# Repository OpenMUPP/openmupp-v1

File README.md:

# OpenMUPP v1 probe board

OpenMUPP v1 is a multi-protocol programming and debug probe.
The design is open hardware.
The board name is `OpenMUPP v1`.
The KiCad 10 project is in this repository.

## What the board does

- It runs **USB CDC, CMSIS-DAP v2 and EDBG (AVR) at the same time** in one firmware image.
- It transfers data **faster than the original Versaloon Mini**. The core runs at 144 MHz, and USB runs at high speed (480 Mbit/s).
- It connects to targets from **1.2 V to 5 V** through level shifters. A 1.2 V target is limited to about 5 MHz.
- It supplies the target with **3.3 V or 5 V (up to about 300 mA)**.
- It makes an adjustable **VPP of 5 V to 14 V** for high-voltage programming of AVR and PIC parts.
- It has **one target connector (J4)**. An adapter board plugs onto J4 and maps it to each target pinout.

## Hardware overview

```mermaid
flowchart LR
    usb["USB-C (J1)"] --> fuse["Polyfuse F1<br/>1.1 A<br/>+5V"]
    fuse --> ldo["3.3 V LDO"]
    fuse --> boost["Boost (U13)<br/>5 V to 14 V"]
    ldo --> mcu["CH32V307RCT6 (U2)<br/>3.3 V"]
    mcu <--> ls["Level shifters<br/>U3 to U6"]
    ls --> esd["33 Ω series resistors<br/>and ESD diodes"]
    esd --> j4["Target connector J4<br/>2 × 10, 2.54 mm"]

    ldo --> tps33["3.3 V target switch<br/>TPS2553 (U12)"]
    fuse --> tps5["5 V target switch<br/>TPS2553 (U14)"]
    tps33 --> vtref(("VTREF"))
    tps5 --> vtref
    vtref --> j4

    boost --> vpp["VPP switch<br/>P-FET (Q2)"]
    vpp --> j4
    pd["Pin 19 pull-down<br/>N-FET (Q6), pull-up to VTREF"] --> j4

    mcu -- "TARGET_PWR_EN" --> tps33
    mcu -- "TARGET_5V_EN" --> tps5
    mcu -- "VPP_12V_ADJ<br/>(DAC: 5 V to 14 V)" --> boost
    mcu -- "VPP_EN, VPP_ON" --> vpp
    mcu -- "VPP_PD" --> pd
    boost -- "VPP_SENSE" --> mcu
```

| Block | Part | Notes |
|-------|------|-------|
| MCU | CH32V307RCT6, LQFP64 (U2) | QingKe V4F RISC-V, 144 MHz, 256 KB flash, 64 KB SRAM. 8 MHz crystal (Y1). |
| USB | USB-C receptacle (J1), USBLC6-2SC6 (U1) | USB 2.0 high speed (USBHS on PB6, PB7). 5.1 kΩ CC resistors. |
| 3.3 V rail | XC6220B331MR-G LDO | Supplies the MCU and the target power switch. |
| VBUS protection | 1.1 A polyfuse (F1), 2.2 A trip, 16 V | At 4.75 V VBUS, expect `+5V` at about 4.6 V or more at full load. See [Target power](docs/hardware.md#target-power). |
| Target power (3.3 V or 5 V) | TPS2553 (U12, 3.3 V), TPS2553 (U14, 5 V), FDV301N interlock (Q4) | Current limit about 300 mA (ILIM 91 kΩ) on each rail. Both outputs join `VTREF`. See [Target power](docs/hardware.md#target-power). |
| VPP (5 V to 14 V) | MT3608 boost (U13), AO3401A P-FET (Q2), FDV301N driver (Q3), MMBT3906 current limit (Q5), FDV301N pull-down (Q6) | The firmware sets the level with the DAC on PA5 (`VPP_12V_ADJ`). Current limit about 17 mA. Pin 19 has three states: 0 V, `VTREF` and VPP. See [High voltage (VPP)](docs/hardware.md#high-voltage-vpp). |
| Level shifters | SN74LXC8T245 (U3, U4), SN74LXC1T45 (U5, U6) | All parts work from 1.1 V to 5.5 V. |
| Reset path | FDV301N (Q1), U4 channel 4 | Q1 pulls nRESET low. U4 reads the line back. |
| ESD | TPD4E05U06 (U8 to U10) | On all J4 signals except the supplies. |
| Probe debug | J3 (5-pin SWD), J2 (3-pin UART) | J3 debugs the probe MCU only. J2 is the log port of the probe firmware. **They are not target connectors.** |
| User I/O | SW1 (key and BOOT0), LEDs D1 (blue) and D4 (red) for state, D2 (green) for USB | |

### Target connector J4

J4 is a 2 × 10 IDC header, 2.54 mm. The footprint in the schematic is `Connector_IDC:IDC-Header_2x10_P2.54mm_Horizontal`. Use a shrouded and keyed header. VPP is on pin 19, so a shifted plug must not fit.

| Pin | Signal | Pin | Signal |
|-----|--------|-----|--------|
| 1 | `VTREF`: target voltage sense, and target supply when the probe powers the target | 2 | Reserved (no connect) |
| 3 | GND | 4 | TMS / SWDIO / data (`DIR_SWDIO`) |
| 5 | GND | 6 | TCK / SWCLK / SCK |
| 7 | GND | 8 | TDO / SWO / MISO |
| 9 | GND | 10 | TDI / MOSI |
| 11 | RTCK | 12 | nRESET / debugWIRE, open-drain |
| 13 | UART TX (probe output) | 14 | UART RX (probe input) |
| 15 | TRST | 16 | Adapter ID (ADC, 3.3 V domain) |
| 17 | `AUX1` | 18 | `AUX2` |
| 19 | VPP (0 V, `VTREF`, or 5 V to 14 V) | 20 | GND |

- **Target power is on pin 1.** One pin carries the sense and the supply. The limit is about 300 mA at 3.3 V and at 5 V.
- **Pin 2 is reserved.** A later adapter that needs a second supply pin can use it, with its own switch.
- **Pin 16 goes to the adapter only.** It never goes to the target.

### Adapter boards and adapter ID

An adapter board has connectors, wires and one ID resistor. The resistor goes from J4 pin 16 to GND. R30 (10 kΩ) pulls pin 16 up to 3.3 V. The firmware reads the ratio x = R<sub>ID</sub> / (R<sub>ID</sub> + 10 kΩ) on PB1. The ADC reference and R30 share the 3.3 V rail, so supply drift cancels. R44 (10 kΩ) in series and D5 (BAT54 Schottky diode) to 3.3 V protect PB1 (net `ADAPTER_ID_MCU`). They work when a 5 V target supply is on pin 16 by mistake. C13 (100 nF) from `ADAPTER_ID_MCU` to GND filters the ADC input. The firmware must use a long ADC sample time and keep the internal pull resistors off.

The AVR 10-pin connector uses the Atmel-ICE pinout. Three passive variants route the data pin to SWDIO:

| Variant | Protocols | Slot |
|---------|-----------|------|
| A | JTAG, ISP, debugWIRE | 1 |
| B | PDI | 2 |
| C | TPI, UPDI, aWire | 3 |

| Slot | R<sub>ID</sub> (E24, 1 %) | x | Accept window | Use |
|------|------------------|-------|---------------|-----|
| — | 0 Ω (short) | 0.000 | below 0.05 | Fault: pin 16 shorted to GND |
| 1 | 1.1 kΩ | 0.099 | 0.05 to 0.15 | Variant A |
| 2 | 2.4 kΩ | 0.194 | 0.15 to 0.25 | Variant B |
| 3 | 4.3 kΩ | 0.301 | 0.25 to 0.35 | Variant C |
| 4 | 6.8 kΩ | 0.405 | 0.35 to 0.45 | Arm adapter |
| 5 | 10 kΩ | 0.500 | 0.45 to 0.55 | Pin-header adapter |
| 6 | 15 kΩ | 0.600 | 0.55 to 0.65 | Free |
| 7 | 24 kΩ | 0.706 | 0.65 to 0.75 | Free |
| 8 | 39 kΩ | 0.796 | 0.75 to 0.85 | AVR high-voltage adapter |
| 9 | 91 kΩ | 0.901 | 0.85 to 0.95 | PIC high-voltage adapter |
| — | open | 1.000 | above 0.95 | No adapter |

The worst-case error is about 0.007 in x, and the windows are ±0.05 wide. The firmware treats a free slot as "unknown adapter". The firmware enables VPP only for slots 8 and 9.

The adapter schematics are in [connectors/](connectors/README.md). Each adapter has a female 2 × 10 header that plugs directly onto J4. No ribbon cable is necessary.

See [docs/hardware.md](docs/hardware.md) for the sheets, level shifting, target power, VPP and the MCU pin map.

## Firmware

The firmware is the `openmupp` project. The CH32V307 has a ROM bootloader. It can program the flash through USART1 or USB (WCH ISP protocol). Hold SW1 (BOOT0) during reset to start it. The firmware port to the CH32V307 is in progress. A firmware jump to the bootloader is not available yet.

Related repositories:

- Firmware: <https://github.com/OpenMUPP/openmupp>
- Drivers: <https://github.com/armint/ch32v00x-system> and <https://github.com/armint/ch32v00x-art>

## Getting started

### Requirements

- KiCad 10.0.6 or newer.
- The shared footprint libraries. They are not public. The PCB file has a copy of each footprint, so you can open and edit the board without them. The project uses the nicknames `resistors`, `capacitors`, `headers`, `connectors`, `inductors` and `sot`. The stock KiCad libraries (`Package_*`, `Connector_IDC`, `Diode_SMD`, `LED_SMD`, `Crystal`, `Fuse`, `Button_Switch_SMD`) must also be present.

### Open the project

1. Clone this repository.
2. Open `openmupp-v1.kicad_pro`.

The board and the schematic open without the shared footprint libraries. To change a footprint, edit the copy in the PCB file.

The project symbol library `openmupp-v1` is in the repository. `sym-lib-table` links it with `${KIPRJMOD}`.

### Conventions

- **Reference designators are unique across all sheets.** Check before you add a part.
- **Every part has an `LCSC` field** for JLCPCB assembly. Prefer parts from the JLCPCB basic library. Each extended part costs a setup fee.
- **Small N-FETs:** use the FDV301N (LCSC C15310). V<sub>GS(th)</sub> is 1.06 V maximum, so a gate drive of 1.8 V turns it on. The limits are 25 V V<sub>DS</sub> and 8 V V<sub>GS</sub>.
- **Footprints:** check the pads against the datasheet land pattern.
- **Checks:** run ERC after each change. Look for shorted nets and for unconnected pins.

## License

Copyright Armin van der Togt 2026.

This design is licensed under the CERN Open Hardware Licence Version 2 - Strongly Reciprocal (CERN-OHL-S-2.0). See [LICENSE](LICENSE).
The design has no warranty. Refer to the licence for the applicable conditions.

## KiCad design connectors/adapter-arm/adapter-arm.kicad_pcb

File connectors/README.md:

# Target adapters for OpenMUPP v1

Each folder is a KiCad 10 project with the schematic of one target adapter. The projects have no board layout yet.

| Folder                                     | Adapter          | Slot | R<sub>ID</sub> | Target connectors                                              |
|--------------------------------------------|------------------|------|----------------|----------------------------------------------------------------|
| [adapter-avr-jtag-isp](adapter-avr-jtag-isp/) | AVR variant A | 1 | 1.1 kΩ | Atmel-ICE 10 (1.27 mm), AVR JTAG 10 (2.54 mm), 2 × 3 ISP |
| [adapter-arm](adapter-arm/)                | Arm              | 4    | 6.8 kΩ         | ARM JTAG 20, Cortex Debug 10, STDC14                           |
| [adapter-pin-header](adapter-pin-header/)  | Pin header       | 5    | 10 kΩ          | 1 × 6 SWD / CH32 / SWIM, 1 × 4 ST SWIM, 2 × 5 WCH-LinkE layout |
| [adapter-avr-hv](adapter-avr-hv/)          | AVR high voltage | 8    | 39 kΩ          | DIP-8 and DIP-14 sockets (HVSP), 2 × 3 TPI and UPDI            |
| [adapter-pic-hv](adapter-pic-hv/)          | PIC high voltage | 9    | 91 kΩ          | PICkit ICSP 1 × 6                                              |

The slot table and the J4 pinout are in the [main README](../README.md#adapter-boards-and-adapter-id).

## Rules for all adapters

1. J1 is a female 2 × 10 header, 2.54 mm. It plugs directly onto J4 of the probe. The pin numbers of J1 are the J4 pin numbers.
2. One 1 % resistor (R1) goes from J1 pin 16 to GND. J1 pin 16 never goes to the target.
3. J1 pin 2 (reserved) stays open. J1 pin 19 (VPP) stays open on each adapter that is not a high-voltage adapter.
4. Each adapter has a 1 × 4 debug UART header: 1 GND, 2 RX (probe input), 3 TX (probe output), 4 `VTREF`. The labels are from the probe side. Pins 1 to 3 have the same order as J2 on the main board. Pin 4 lets the UART work without a debug connector to the target.
5. Connect only one target connector at a time.

## Female header on J4

J4 on the probe is a shrouded, right-angle header (`IDC-Header_2x10_P2.54mm_Horizontal`). The adapter schematics use `PinSocket_2x10_P2.54mm_Horizontal` for J1, so the adapter board is in the same plane as the probe. Before layout, check these items:

- **Fit.** The socket body must go into the shroud of J4. Measure the shroud opening and the socket body.
- **Pin mirror.** The socket and the header mate face to face. Make sure that J1 pin 1 touches J4 pin 1 in the layout.
- **Polarity.** A plain socket has no key, so it can go in rotated by 180°. Then J1 pin 16 touches a probe GND pin, and the probe pin 16 touches an adapter GND pin. The adapter ID reads 0 Ω (the fault slot). The firmware must then keep the shifter outputs, the target power and VPP off. Use a keyed socket, or add a mechanical key on the adapter board, if possible.

## RESET and MCLR on J4 pin 19

`adapter-avr-hv` and `adapter-pic-hv` connect the target RESET or MCLR pin directly to J1 pin 19. The nets are `RESET_VPP` and `MCLR_VPP`. The probe gives pin 19 three levels: 0 V (reset), `VTREF` (run) and VPP (program). See [Pin 19 states](../docs/hardware.md#pin-19-states). Thus the adapters have no reset circuit, and J1 pin 18 (`AUX2`) is not used.

HVSP entry needs RESET at 0 V while `VCC` comes up. Then RESET must go to 12 V after a short time. Q6 on the probe holds pin 19 at 0 V. The firmware can set `VPP_ON` before `VCC` comes up, because Q6 holds pin 19 low against the current limit. Then the firmware releases Q6 at the time that the data sheet gives. Pin 19 then goes to VPP in some µs.

## UPDI on J4 pin 12

UPDI uses J4 pin 12 (nRESET / debugWIRE), not J4 pin 4 (SWDIO). The reasons:

- The UPDI pin of a tinyAVR is a weak driver. The ATtiny1614/16/17 data sheet (DS40002204A, table 36-16, VOL2) guarantees only 0.1 mA at 1.8 V and 0.5 mA at 5 V.
- J4 pin 4 has a 2.2 kΩ pull-up on the probe. The target must then sink 0.8 mA to 2.3 mA. See issue [#6](https://github.com/OpenMUPP/openmupp-v1/issues/6).
- J4 pin 12 has a 10 kΩ pull-up. The target must sink 0.18 mA at 1.8 V and 0.5 mA at 5 V.
- J4 pin 12 is open-drain (Q1 on the probe). This is the physical layer that UPDI expects.

Effects on the firmware:

- The read-back of J4 pin 12 goes to PB11 (USART3_RX). The USART receives UPDI and sees its own transmit.
- The CH32V307 USART cannot invert TX, so the firmware sends UPDI in software through Q1 (PB12). debugWIRE uses the same method.
- The rise time with 10 kΩ and about 30 pF to 50 pF is about 0.3 µs to 0.5 µs. This is sufficient for 225 kbps (the maximum UPDI rate at 1.8 V). It is not sufficient for 0.9 Mbps. These values are estimates, not measurements.
- The debug UART (J4 pins 13 and 14) stays free during UPDI.

On `adapter-avr-hv`, TPI data also uses J4 pin 12, through the same path as UPDI. The TPIDATA pin of the ATtiny4/5/9/10 has an internal pull-up in TPI mode (20 kΩ to 50 kΩ). The target drives a 0 and the first 1 of a sequence. Then the pull-up holds the line high (ATtiny4/5/9/10 data sheet DS40002060A, section 15.3.8). Thus TPI and UPDI see the same physical layer: open drain with a pull-up. Other TPI adapters can still use J4 pin 4.

## UPDI high-voltage pulse

`adapter-avr-hv` has one 2 × 3 header (J4) for TPI and UPDI. JP1, a 2-pin jumper header, selects the pin that gets the high voltage (HV):

| JP1 | Use | Pin 1 (data) | Pin 5 | HV goes to |
|-----|-----|--------------|-------|------------|
| Open | TPI (ATtiny4/5/9/10). UPDI with a separate RESET pin, for example AVR DD. | `UPDI_HV` (through Q2 to J1 pin 12) | `RESET_VPP` (J1 pin 19) | Pin 5 |
| Closed | UPDI with HV on the UPDI pin (tinyAVR 0, 1 and 2 series) | `UPDI_HV` (through Q2 to J1 pin 12) | `RESET_VPP` (J1 pin 19) | Pin 1 and pin 5 |

On the tinyAVR 0, 1 and 2 series, the UPDI pin and the RESET pin are the same pin. The data sheet calls the HV entry "UPDI Enable with High-Voltage Override of RESET Pin". The HV detection level (V<sub>HVRST</sub>) is 11.5 V to 12.5 V. The AVR DD setting is not verified against a part. Check the data sheet of each part before you use it.

The TPIDATA pin and the AVR DD UPDI pin must not get 12 V. Thus JP1 must be open for these parts. With JP1 closed, pin 5 also gets VPP. On a tinyAVR target board, pin 5 is usually not connected, so this is permitted. Some target boards connect pin 5 to the UPDI pin. Then pin 19 at 0 V holds the UPDI line low. Check the target board before you use it.

The parts of the UPDI path:

1. D2 (BAT54W) and JP1 connect J1 pin 19 to `UPDI_HV` when JP1 is closed. D2 has a drop of about 0.3 V. Set VPP to about 12.3 V for 12 V on the UPDI pin. `RESET_VPP` has no diode, so it gets VPP directly.
2. Q2 (FDV301N) is a pass switch between `UPDI_HV` (drain) and `UPDI` (source, J1 pin 12). The gate is on `VTREF`. When `UPDI_HV` is at 12 V, Q2 is off and the 10 kΩ pull-up on the probe holds `UPDI` at `VTREF`. The body diode is then reverse biased. The ESD diode on J4 pin 12 of the probe clamps at about 6 V, so this protection is necessary.
3. While VPP is off, Q2 passes UPDI and TPI data in both directions. The probe pulls `UPDI` high (10 kΩ). The internal pull-up of the target pulls `UPDI_HV` high. The adapter has no pull-up on `UPDI_HV`, so it adds no load to the weak UPDI pad.
4. With JP1 closed, keep pin 19 at 0 V (`VPP_PD` high) during UPDI, except during the HV pulse. In the run state, pin 19 is at `VTREF`. Then R39 on the probe and D2 pull `UPDI_HV` up. When the target sends a 0, it must also sink this current: about 0.13 mA at 1.8 V and 0.45 mA at 5 V. The UPDI pad guarantees only 0.1 mA at 1.8 V. At 0 V on pin 19, D2 blocks and adds no load.
5. The firmware can read the JP1 position before it sets VPP on. Put pin 19 in the run state and set Q1 on. With JP1 closed, current flows from R39 through D2, Q2 and Q1. `VPP_SENSE2` then reads less than about 0.5 V. With JP1 open, `VPP_SENSE2` reads the run level. If the JP1 position does not agree with the selected target, the firmware must not set VPP on. This value is an estimate, not a measurement.

Limits:

- Q2 passes a low level only when `VTREF` is above V<sub>GS(th)</sub>. The FDV301N has 1.06 V maximum, so `VTREF` of 1.8 V is sufficient. The tinyAVR parts run from 1.8 V to 5.5 V.
- The gate-source voltage of the FDV301N must stay above −0.3 V. The source (`UPDI`) has a 10 kΩ pull-up to the gate potential (`VTREF`), so it does not go above the gate. Q2 leakage (I<sub>DSS</sub> 1 µA maximum at 20 V) moves `UPDI` by about 10 mV.
- A low-to-high edge on `UPDI_HV` above `VTREF` − V<sub>GS(th)</sub> comes from the target pull-up only. This is slower than on `UPDI`. Check the rise time at the UPDI baud rate and at the TPI clock rate.
- VPP goes to `RESET_VPP`. With JP1 closed, it also goes to `UPDI_HV` at the same time. Connect only one target to J2, J3 or J4.
- After the pulse, the line must return to the normal level quickly: the debugger drives it low 1 µs to 10 µs after the HV ends (data sheet figure 33-6). D2 cannot pull `UPDI_HV` down. The probe pulls J4 pin 12 low through its Q1. The adapter Q2 then conducts, because its gate is at `VTREF`, and pulls `UPDI_HV` low. At the same time, Q6 on the probe pulls pin 19 to 0 V in less than 1 µs, so D2 blocks at once.
- The TPS2553 on the probe has a soft start of some milliseconds. Check the pulse timing in the target data sheet.

## HVSP pull-downs

HVSP entry needs the three Prog_enable pins at 0 while `VCC` comes up. R4 to R7 (10 kΩ) hold them low on `adapter-avr-hv`. These resistors are not in the adapter plan. The pins come from the ATtiny datasheets:

| Part              | Prog_enable[0..2]           | Resistors                                          |
|-------------------|-----------------------------|----------------------------------------------------|
| ATtiny13/25/45/85 | SDI, SII, SDO (PB0 to PB2)  | The probe drives SDI and SII low. R4 holds SDO low |
| ATtiny24A/44A/84A | PA0, PA1, PA2 (pins 13, 12, 11) | R5, R6, R7                                     |

J4 pin 8 (SDO input) is an input only, so the probe cannot hold SDO low. The target drives SDO against R4 after entry.

## Items to check before layout

- **WCH-LinkE layout.** The positions of GND, 3V3 and 5V on the WCH-LinkE header come from the schematic text only. Check them on a real WCH-LinkE. Pin 8 (3V3) connects to `VTREF`. Pin 10 (5V) stays open.
- **ST SWIM order.** Check the order (VDD, SWIM, GND, NRST) against ST UM1075.
- **1.27 mm headers.** Cortex Debug 10 and STDC14 use plain 1.27 mm pin headers in the schematic. Use shrouded, keyed parts (Samtec FTSH-105 and FTSH-107, or equal). Put their footprints in the `kicad-footprints` repository.
- **Atmel-ICE 10.** J2 on `adapter-avr-jtag-isp` is a plain 1.27 mm pin header in the schematic. Use a shrouded, keyed part, as for Cortex Debug 10. J4 (AVR JTAG 10, 2.54 mm) uses a shrouded IDC header.
- **Footprint libraries.** All resistors are 0603 and use `resistors:R_0603` from the `kicad-footprints` repository, as on the main board.

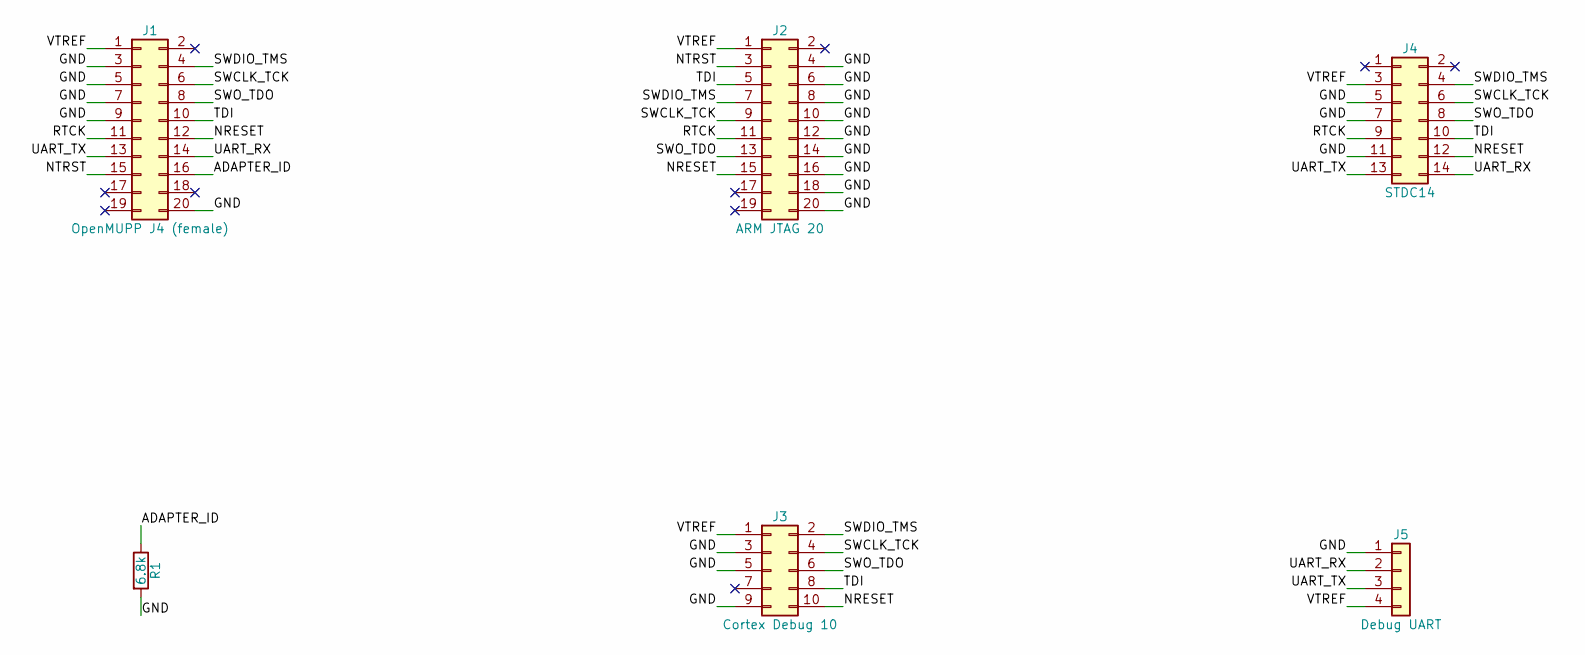
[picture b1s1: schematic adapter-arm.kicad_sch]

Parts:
J1: OpenMUPP J4 (female); PinSocket_2x10_P2.54mm_Horizontal
J2: ARM JTAG 20; IDC-Header_2x10_P2.54mm_Vertical
J3: Cortex Debug 10; PinHeader_2x05_P1.27mm_Vertical_SMD
J4: STDC14; PinHeader_2x07_P1.27mm_Vertical_SMD
J5: Debug UART; PinHeader_1x04_P2.54mm_Vertical
R1: 6.8k; R_0603

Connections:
/ADAPTER_ID: J1.16, R1.1
/GND: J1.3, J1.5, J1.7, J1.9, J1.20, J2.4, J2.6, J2.8, J2.10, J2.12, J2.14, J2.16, J2.18, J2.20, J3.3, J3.5, J3.9, J4.5, J4.7, J4.11, J5.1, R1.2
/NRESET: J1.12, J2.15, J3.10, J4.12
/NTRST: J1.15, J2.3
/RTCK: J1.11, J2.11, J4.9
/SWCLK_TCK: J1.6, J2.9, J3.4, J4.6
/SWDIO_TMS: J1.4, J2.7, J3.2, J4.4
/SWO_TDO: J1.8, J2.13, J3.6, J4.8
/TDI: J1.10, J2.5, J3.8, J4.10
/UART_RX: J1.14, J4.14, J5.2
/UART_TX: J1.13, J4.13, J5.3
/VTREF: J1.1, J2.1, J3.1, J4.3, J5.4

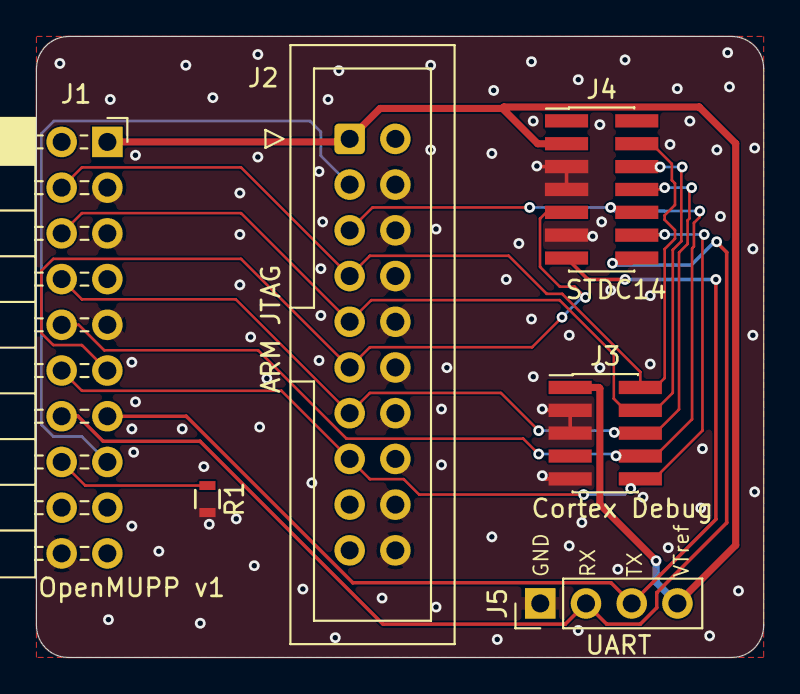
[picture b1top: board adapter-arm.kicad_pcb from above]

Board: 2 copper layers, 40.4 x 34.5 mm, 6 parts (0 on the bottom side), 12 nets.

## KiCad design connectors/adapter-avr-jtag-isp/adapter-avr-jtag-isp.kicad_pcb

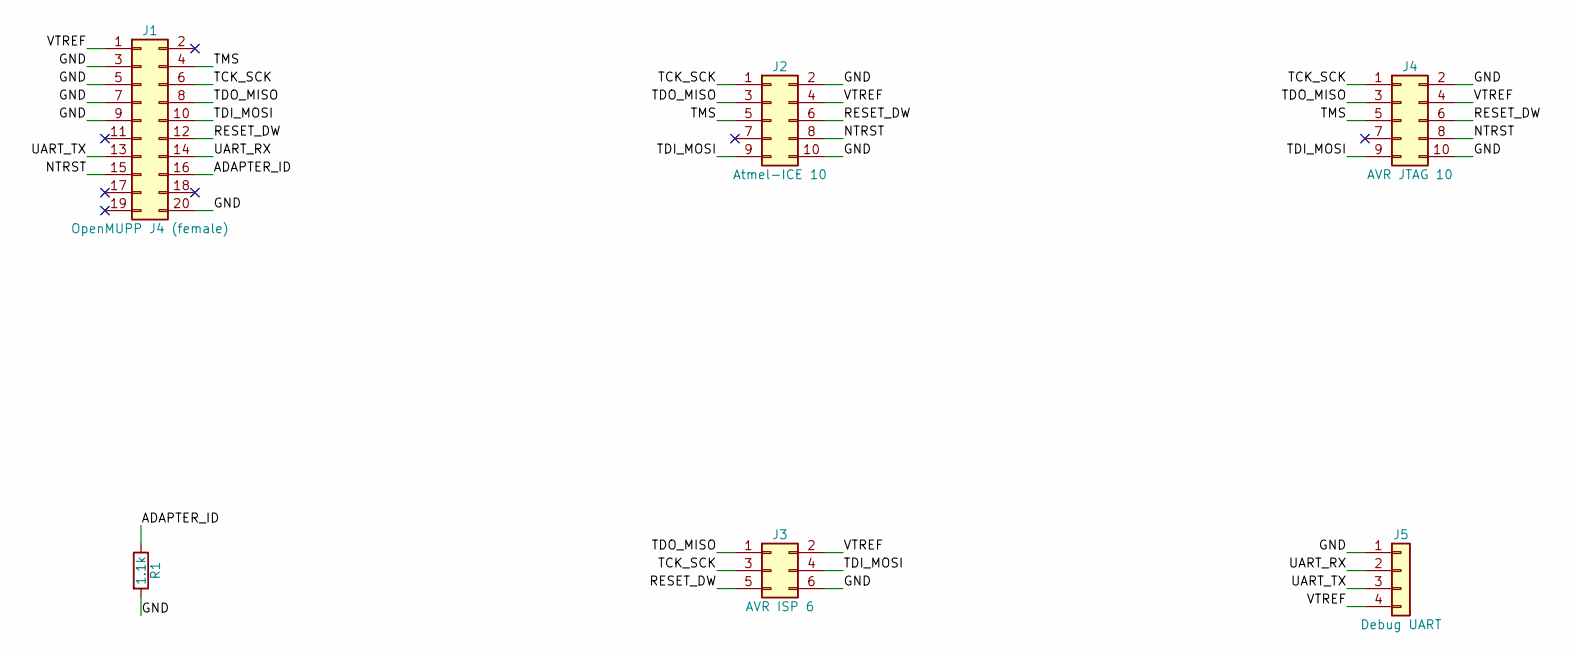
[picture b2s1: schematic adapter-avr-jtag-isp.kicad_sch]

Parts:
J1: OpenMUPP J4 (female); PinSocket_2x10_P2.54mm_Horizontal
J2: Atmel-ICE 10; PinHeader_2x05_P1.27mm_Vertical_SMD
J3: AVR ISP 6; PinHeader_2x03_P2.54mm_Vertical
J4: AVR JTAG 10; IDC-Header_2x05_P2.54mm_Vertical
J5: Debug UART; PinHeader_1x04_P2.54mm_Vertical
R1: 1.1k; R_0603

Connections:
/ADAPTER_ID: J1.16, R1.1
/GND: J1.3, J1.5, J1.7, J1.9, J1.20, J2.2, J2.10, J3.6, J4.2, J4.10, J5.1, R1.2
/NTRST: J1.15, J2.8, J4.8
/RESET_DW: J1.12, J2.6, J3.5, J4.6
/TCK_SCK: J1.6, J2.1, J3.3, J4.1
/TDI_MOSI: J1.10, J2.9, J3.4, J4.9
/TDO_MISO: J1.8, J2.3, J3.1, J4.3
/TMS: J1.4, J2.5, J4.5
/UART_RX: J1.14, J5.2
/UART_TX: J1.13, J5.3
/VTREF: J1.1, J2.4, J3.2, J4.4, J5.4

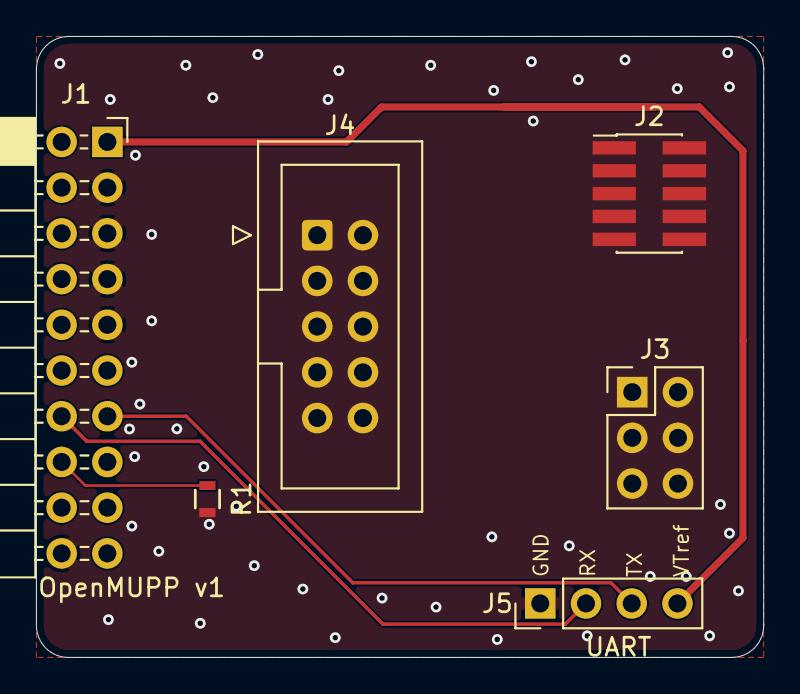
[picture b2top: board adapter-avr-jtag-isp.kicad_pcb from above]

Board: 2 copper layers, 40.4 x 34.5 mm, 6 parts (0 on the bottom side), 11 nets.

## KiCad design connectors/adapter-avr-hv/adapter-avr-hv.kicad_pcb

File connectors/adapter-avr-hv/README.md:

# adapter-avr-hv

This adapter programs AVR parts that need a high voltage (12 V) on one pin. This is necessary when a fuse disables the normal programming interface. Examples are the RSTDISBL fuse and the RSTPINCFG fuse. The adapter has slot 8 (R1 = 39 kΩ).

The probe supplies all levels on J1 pin 19: 0 V, `VTREF` and VPP. See [Pin 19 states](../../docs/hardware.md#pin-19-states). The circuit details are in [connectors/README.md](../README.md).

## Connectors

| Ref | Type | Interface | Target parts | 12 V goes to |
|-----|------|-----------|--------------|--------------|
| J1 | 2 × 10 socket | Probe J4 | — | — |
| J2 | DIP-8 socket | HVSP | ATtiny13, ATtiny25/45/85 | Pin 1 (RESET) |
| J3 | DIP-14 socket | HVSP | ATtiny24/44/84 | Pin 4 (RESET) |
| J4 | 2 × 3 header | TPI and UPDI | ATtiny4/5/9/10, tinyAVR 0, 1 and 2 series, AVR DD | Pin 5 (RESET). With JP1 closed, also pin 1 (UPDI). |
| J5 | 1 × 4 header | Debug UART | Any | — |
| JP1 | 2-pin jumper header | HV select for J4 | — | — |

HVSP is high-voltage serial programming. TPI is the Tiny Programming Interface. UPDI is the Unified Program and Debug Interface.

Connect only one target at a time. VPP goes to J2, J3 and J4 at the same time.

### J2 and J3: HVSP sockets

Put the part directly into the socket. The probe supplies `VCC` from `VTREF`.

| HVSP signal | J1 pin | J2 (DIP-8) | J3 (DIP-14) |
|-------------|--------|------------|-------------|
| RESET (12 V) | 19 | 1 (PB5) | 4 (PB3) |
| SCI (clock) | 6 | 2 (PB3) | 2 (PB0) |
| SDI (data in) | 10 | 5 (PB0) | 7 (PA6) |
| SII (instruction in) | 17 | 6 (PB1) | 8 (PA5) |
| SDO (data out) | 8 | 7 (PB2) | 9 (PA4) |
| `VCC` | 1 | 8 | 1 |
| GND | 3, 5, 7, 9, 20 | 4 | 14 |

HVSP entry needs three Prog_enable pins at 0 while `VCC` comes up. On J2, these pins are SDI, SII and SDO. The probe drives SDI and SII low, and R4 holds SDO low. On J3, these pins are PA0, PA1 and PA2 (pins 13, 12 and 11). R7, R6 and R5 hold them low. The pin data is from the ATtiny25/45/85 data sheet (table 20-13) and the ATtiny24A/44A/84A data sheet (table 19-13).

### J4: TPI and UPDI header

J4 uses the Microchip 6-pin layout for TPI and UPDI (Atmel-ICE user guide, tables 3-4 and 3-7).

| Pin | Function | Net | J1 pin |
|-----|----------|-----|--------|
| 1 | TPI data or UPDI | `UPDI_HV` | 12, through Q2 |
| 2 | `VTREF` | `VTREF` | 1 |
| 3 | TPI clock | `SCI_TPICLK` | 6 |
| 4 | — | Open | — |
| 5 | RESET | `RESET_VPP` | 19 |
| 6 | GND | GND | GND |

TPI data and UPDI use the same pin, J1 pin 12. The probe drives this pin open drain, with a 10 kΩ pull-up. The target pulls `UPDI_HV` high with its internal pull-up. See [UPDI on J4 pin 12](../README.md#updi-on-j4-pin-12).

### JP1: HV select

JP1 selects the J4 pin that gets 12 V. Set JP1 before you connect the target.

| JP1 | 12 V on | Use for |
|-----|---------|---------|
| Open | Pin 5 only | TPI (ATtiny4/5/9/10). UPDI parts with a separate RESET pin, for example AVR DD. |
| Closed | Pin 1 (through D2) and pin 5 | tinyAVR 0, 1 and 2 series. UPDI and RESET are on the same pin. |

**CAUTION:** Do not close JP1 for a TPI part or an AVR DD part. Pin 1 then gets 12 V, and this can damage the part.

- TPI needs 12 V on RESET only when the RSTDISBL fuse is programmed.
- The AVR DD setting is not verified against a part. Read the data sheet of the part before you use it.
- With JP1 closed, pin 5 also gets VPP. Some tinyAVR target boards connect pin 5 to the UPDI pin. Check the target board before you use it.
- The firmware can read the JP1 position before it sets VPP on. See [UPDI high-voltage pulse](../README.md#updi-high-voltage-pulse).

### J5: debug UART

| Pin | Signal | J1 pin |
|-----|--------|--------|
| 1 | GND | GND |
| 2 | RX (probe input) | 14 |
| 3 | TX (probe output) | 13 |
| 4 | `VTREF` | 1 |

All adapters have this header (see [Rules for all adapters](../README.md#rules-for-all-adapters)).

## Other parts

| Ref | Value | Function |
|-----|-------|----------|
| R1 | 39 kΩ | Adapter ID, slot 8 |
| D2 | BAT54W | With JP1 closed, connects `RESET_VPP` to `UPDI_HV` (J4 pin 1). It blocks while pin 19 is at 0 V. |
| Q2 | FDV301N | Pass switch between `UPDI_HV` and `UPDI`. It blocks 12 V from J1 pin 12. |
| R4 | 10 kΩ | Holds SDO (J2 pin 7) low at HVSP entry |
| R5, R6, R7 | 10 kΩ | Hold PA0, PA1 and PA2 on J3 low at HVSP entry |

J1 pins 2, 4, 11, 15 and 18 are not used.

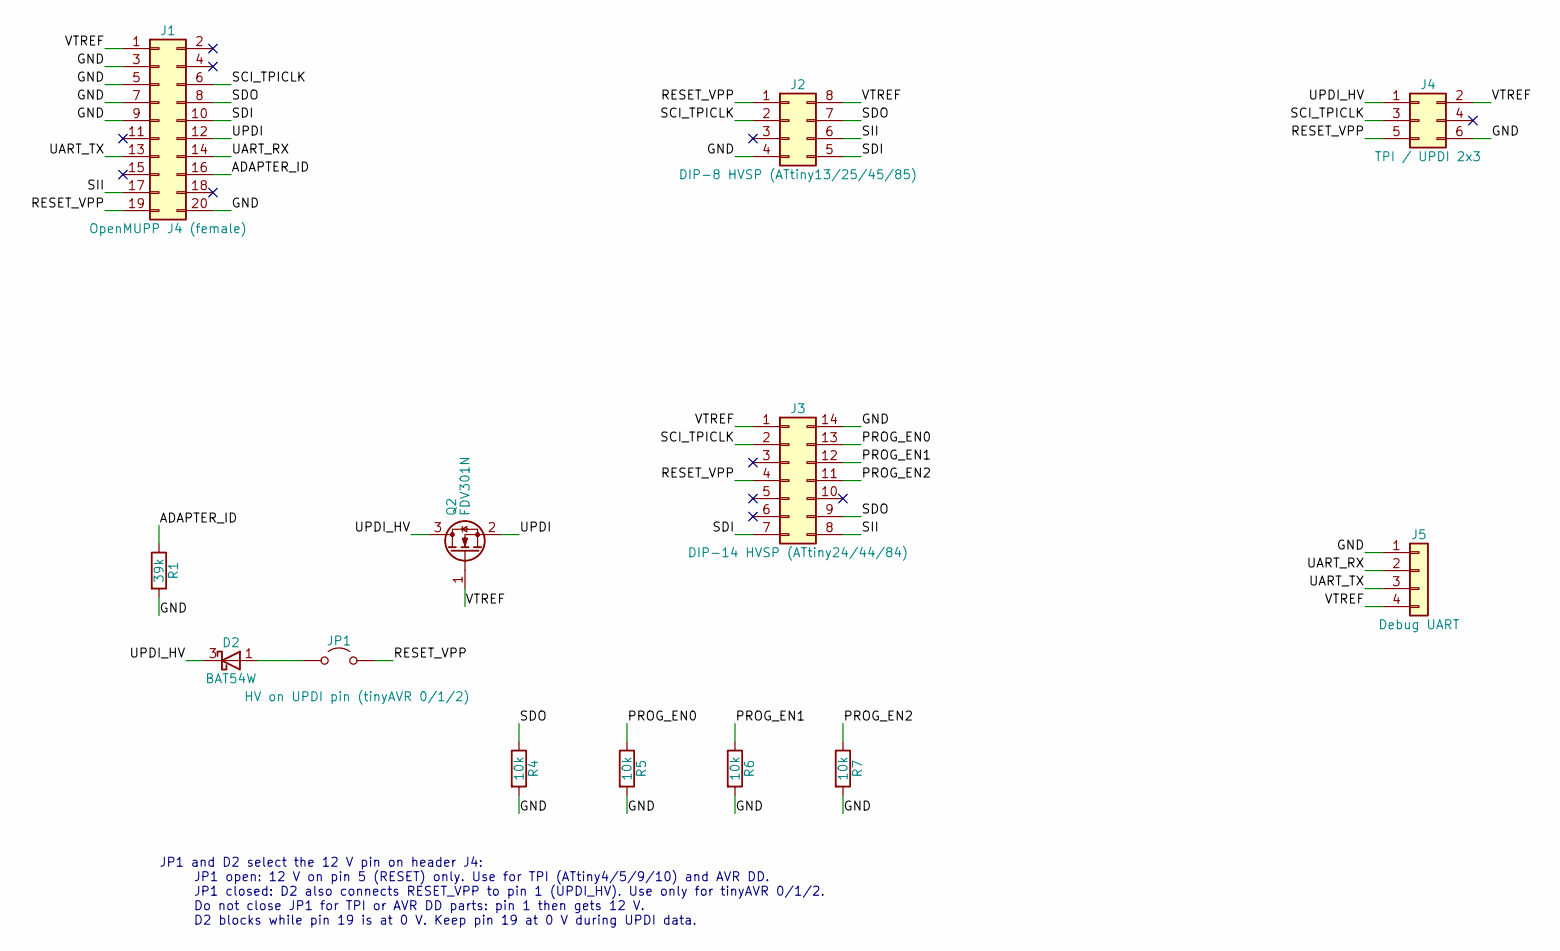
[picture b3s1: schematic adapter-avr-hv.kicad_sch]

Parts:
D2: BAT54W; SOT-323_SC-70
J1: OpenMUPP J4 (female); PinSocket_2x10_P2.54mm_Horizontal
J2: DIP-8 HVSP (ATtiny13/25/45/85); DIP-8_W7.62mm_Socket
J3: DIP-14 HVSP (ATtiny24/44/84); DIP-14_W7.62mm_Socket
J4: TPI / UPDI 2x3; PinHeader_2x03_P2.54mm_Vertical
J5: Debug UART; PinHeader_1x04_P2.54mm_Vertical
JP1: HV on UPDI pin (tinyAVR 0/1/2); PinHeader_1x02_P2.54mm_Vertical
Q2: FDV301N; SOT-23
R1: 39k; R_0603
R4, R5, R6, R7: 10k; R_0603

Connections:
/ADAPTER_ID: J1.16, R1.1
/GND: J1.3, J1.5, J1.7, J1.9, J1.20, J2.4, J3.14, J4.6, J5.1, R1.2, R4.2, R5.2, R6.2, R7.2
/PROG_EN0: J3.13, R5.1
/PROG_EN1: J3.12, R6.1
/PROG_EN2: J3.11, R7.1
/RESET_VPP: J1.19, J2.1, J3.4, J4.5, JP1.2 (B)
/SCI_TPICLK: J1.6, J2.2, J3.2, J4.3
/SDI: J1.10, J2.5, J3.7
/SDO: J1.8, J2.7, J3.9, R4.1
/SII: J1.17, J2.6, J3.8
/UART_RX: J1.14, J5.2
/UART_TX: J1.13, J5.3
/UPDI: J1.12, Q2.2 (S)
/UPDI_HV: D2.3 (K), J4.1, Q2.3 (D)
/VTREF: J1.1, J2.8, J3.1, J4.2, J5.4, Q2.1 (G)
unnamed: D2.1 (A), JP1.1 (A)

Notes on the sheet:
JP1 and D2 select the 12 V pin on header J4: JP1 open: 12 V on pin 5 (RESET) only. Use for TPI (ATtiny4/5/9/10) and AVR DD. JP1 closed: D2 also connects RESET_VPP to pin 1 (UPDI_HV). Use only for tinyAVR 0/1/2. Do not close JP1 for TPI or AVR DD parts: pin 1 then gets 12 V. D2 blocks while pin 19 i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

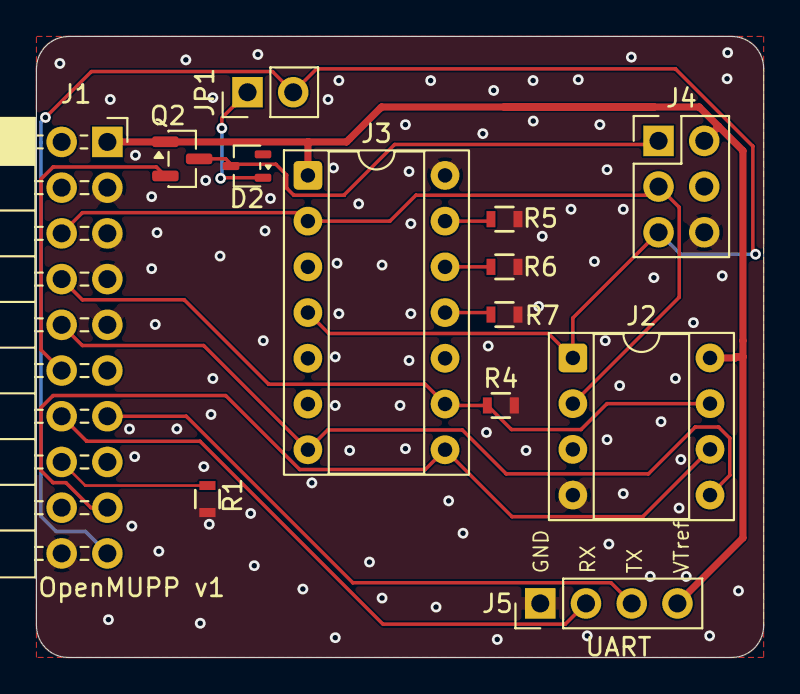
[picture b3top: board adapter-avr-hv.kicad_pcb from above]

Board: 2 copper layers, 40.4 x 34.5 mm, 13 parts (0 on the bottom side), 16 nets.

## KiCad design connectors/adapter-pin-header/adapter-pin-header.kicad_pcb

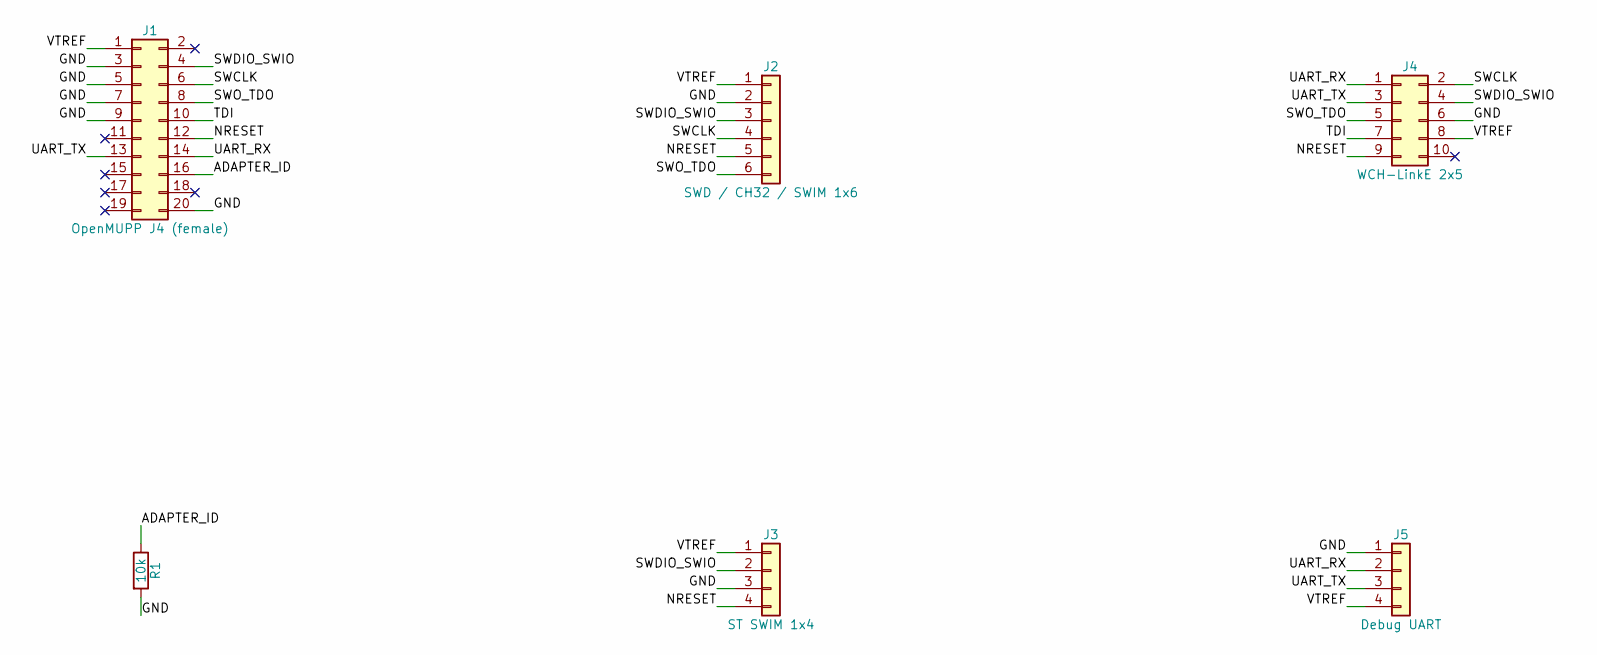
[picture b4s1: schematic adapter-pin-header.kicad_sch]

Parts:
J1: OpenMUPP J4 (female); PinSocket_2x10_P2.54mm_Horizontal
J2: SWD / CH32 / SWIM 1x6; PinHeader_1x06_P2.54mm_Vertical
J3: ST SWIM 1x4; PinHeader_1x04_P2.54mm_Vertical
J4: WCH-LinkE 2x5; PinHeader_2x05_P2.54mm_Vertical
J5: Debug UART; PinHeader_1x04_P2.54mm_Vertical
R1: 10k; R_0603

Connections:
/ADAPTER_ID: J1.16, R1.1
/GND: J1.3, J1.5, J1.7, J1.9, J1.20, J2.2, J3.3, J4.6, J5.1, R1.2
/NRESET: J1.12, J2.5, J3.4, J4.9
/SWCLK: J1.6, J2.4, J4.2
/SWDIO_SWIO: J1.4, J2.3, J3.2, J4.4
/SWO_TDO: J1.8, J2.6, J4.5
/TDI: J1.10, J4.7
/UART_RX: J1.14, J4.1, J5.2
/UART_TX: J1.13, J4.3, J5.3
/VTREF: J1.1, J2.1, J3.1, J4.8, J5.4

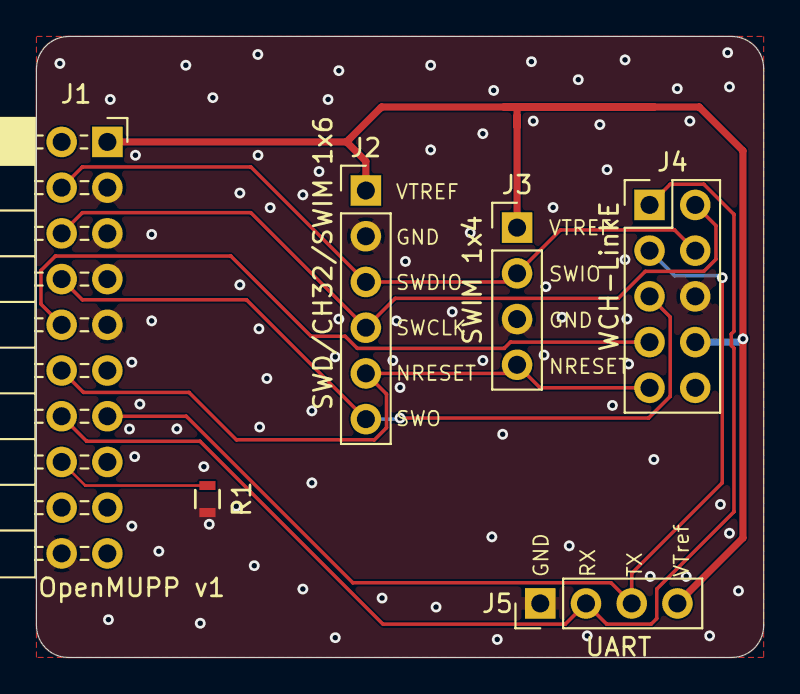
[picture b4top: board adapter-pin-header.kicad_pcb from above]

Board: 2 copper layers, 40.4 x 34.5 mm, 6 parts (0 on the bottom side), 10 nets.

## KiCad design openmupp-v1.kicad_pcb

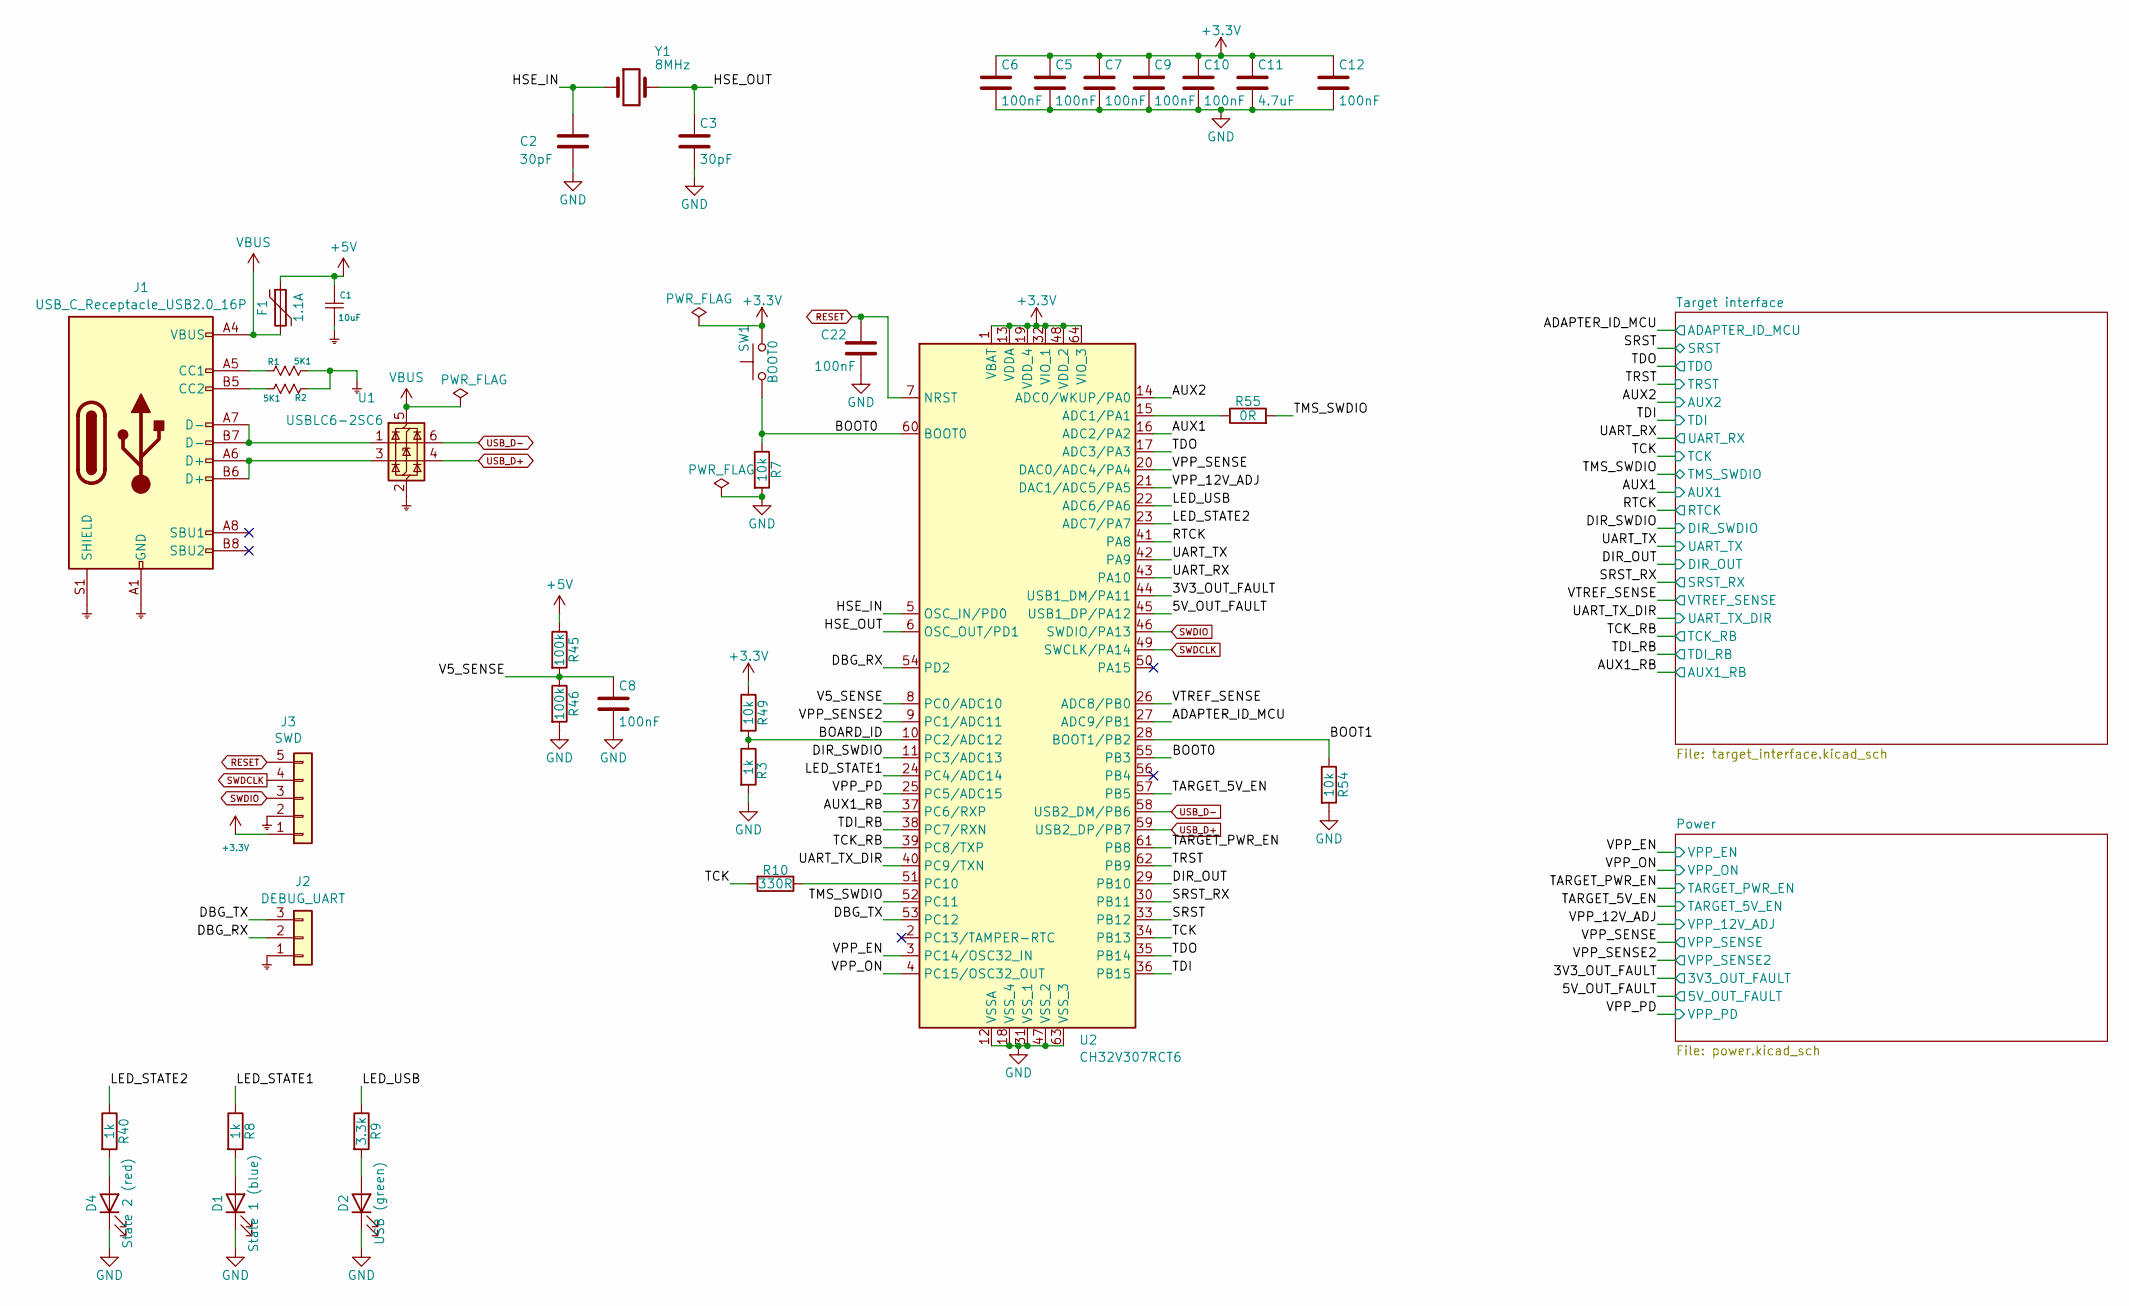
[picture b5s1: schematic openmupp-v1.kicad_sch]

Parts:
C1: 10uF; C_1206; VoltageRating 50V; LCSC C13585
C2, C3: 30pF; C_0402_1005Metric; LCSC C1570
C5, C6, C7, C8, C9, C10, C12, C22: 100nF; C_0603; LCSC C14663
C11: 4.7uF; C_0603; LCSC C19666
D1: State 1 (blue); LED_0603_1608Metric; LCSC C2288
D2: USB (green); LED_0603_1608Metric; LCSC C12624
D4: State 2 (red); LED_0603_1608Metric; LCSC C2286
F1: 1.1A; Fuse_1206_3216Metric; LCSC C7542961
J1: USB_C_Receptacle_USB2.0_16P; USB_C_Receptacle_HRO_TYPE-C-31-M-12; LCSC C165948
J2: DEBUG_UART; PinHeader_1x03_P2.54mm_Vertical
J3: SWD; PinHeader_1x05_P2.54mm_Vertical
R1, R2: 5K1; R_0402; LCSC C25905
R3, R8, R40: 1k; R_0402; LCSC C11702
R7, R49, R54: 10k; R_0402; LCSC C25744
R9: 3.3k; R_0402; LCSC C25890
R10: 330R; R_0603; LCSC C25104
R45, R46: 100k; R_0402; LCSC C25741
R55: 0R; R_0603; LCSC C17168
SW1: BOOT0; SW_Push_HanElectricity_TS1109_4.5x4.5mm_H3.8mm; LCSC C22375347
U1: USBLC6-2SC6; SOT-23-6; LCSC C7519
U2: CH32V307RCT6; TQFP-64_10x10mm_P0.5mm; LCSC C2988083
Y1: 8MHz; Crystal_SMD_5032-2Pin_5.0x3.2mm; MPN X50328MSB2GI; LCSC C115962

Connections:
/3V3_OUT_FAULT: U2.44 (USB1_DM/PA11); also elsewhere on the board
/5V_OUT_FAULT: U2.45 (USB1_DP/PA12); also elsewhere on the board
/ADAPTER_ID_MCU: U2.27 (ADC9/PB1); also elsewhere on the board
/AUX1: U2.16 (ADC2/PA2); also elsewhere on the board
/AUX1_RB: U2.37 (PC6/RXP); also elsewhere on the board
/AUX2: U2.14 (ADC0/WKUP/PA0); also elsewhere on the board
/BOARD_ID: R3.1, R49.2, U2.10 (PC2/ADC12)
/BOOT0: R7.1, SW1.1, U2.55 (PB3), U2.60 (BOOT0)
/BOOT1: R54.1, U2.28 (BOOT1/PB2)
/DBG_RX: J2.2, U2.54 (PD2)
/DBG_TX: J2.3, U2.53 (PC12)
/DIR_OUT: U2.29 (PB10); also elsewhere on the board
/DIR_SWDIO: U2.11 (PC3/ADC13); also elsewhere on the board
/HSE_IN: C2.1, U2.5 (OSC_IN/PD0), Y1.1
/HSE_OUT: C3.1, U2.6 (OSC_OUT/PD1), Y1.2
/LED_STATE1: R8.1, U2.24 (PC4/ADC14)
/LED_STATE2: R40.1, U2.23 (ADC7/PA7)
/LED_USB: R9.1, U2.22 (ADC6/PA6)
/RTCK: U2.41 (PA8); also elsewhere on the board
/SRST: U2.33 (PB12); also elsewhere on the board
/SRST_RX: U2.30 (PB11); also elsewhere on the board
/TARGET_5V_EN: U2.57 (PB5); also elsewhere on the board
/TARGET_PWR_EN: U2.61 (PB8); also elsewhere on the board
/TCK: R10.2, U2.34 (PB13); also elsewhere on the board
/TCK_RB: U2.39 (PC8/TXP); also elsewhere on the board
/TDI: U2.36 (PB15); also elsewhere on the board
/TDI_RB: U2.38 (PC7/RXN); also elsewhere on the board
/TDO: U2.17 (ADC3/PA3), U2.35 (PB14); also elsewhere on the board
/TMS_SWDIO: R55.2, U2.52 (PC11); also elsewhere on the board
/TRST: U2.62 (PB9); also elsewhere on the board
/UART_RX: U2.43 (PA10); also elsewhere on the board
/UART_TX: U2.42 (PA9); also elsewhere on the board
/UART_TX_DIR: U2.40 (PC9/TXN); also elsewhere on the board
/V5_SENSE: C8.1, R45.2, R46.1, U2.8 (PC0/ADC10)
/VPP_12V_ADJ: U2.21 (DAC1/ADC5/PA5); also elsewhere on the board
/VPP_EN: U2.3 (PC14/OSC32_IN); also elsewhere on the board
/VPP_ON: U2.4 (PC15/OSC32_OUT); also elsewhere on the board
/VPP_PD: U2.25 (PC5/ADC15); also elsewhere on the board
/VPP_SENSE: U2.20 (DAC0/ADC4/PA4); also elsewhere on the board
/VPP_SENSE2: U2.9 (PC1/ADC11); also elsewhere on the board
/VTREF_SENSE: U2.26 (ADC8/PB0); also elsewhere on the board
unnamed: D1.2 (A), R8.2
unnamed: D2.2 (A), R9.2
unnamed: D4.2 (A), R40.2
unnamed: J1.A5 (CC1), R1.1
unnamed: J1.B5 (CC2), R2.2
unnamed: J1.A6 (D+), J1.B6 (D+), U1.3 (I/O2)
unnamed: J1.A7 (D-), J1.B7 (D-), U1.1 (I/O1)
unnamed: R55.1, U2.15 (ADC1/PA1)
unnamed: R10.1, U2.51 (PC10)
RESET: C22.1, J3.5, U2.7 (NRST)
SWDCLK: J3.4, U2.49 (SWCLK/PA14)
SWDIO: J3.3, U2.46 (SWDIO/PA13)
USB_D+: U1.4 (I/O2), U2.59 (USB2_DP/PB7)
USB_D-: U1.6 (I/O1), U2.58 (USB2_DM/PB6)

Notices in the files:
openmupp-v1.kicad_pcb:
©2026 ArT BV
parts and their libraries:
copyright: 2018 Armin van der Togt
